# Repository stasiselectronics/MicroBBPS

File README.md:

# MicroBBPS
<h3> Integrated Micro Breadboard Power Supply</h3>
  
Here is the repository for the integrated version of the MicroBBPS. This design shares the same schematic and the same component placement as the solderless version. 

What makes this design special is that it has 26 rows of breadboard spaced plated through holes. This means you can take your breadboard experiments and directly transfer them to the integrated MicroBBPS to build a robust prototype that has easy power entry.

If you want to learn more about this particular version, be sure to check out the documentation webiste.

<h3><a href="https://stasiselectronics.github.io/MicroBBPS/">Read the Docs</a></h3>

<h4><a href="https://github.com/stasiselectronics/MicroBBPS/tree/main">Back to the solderless version repository</a></h4>

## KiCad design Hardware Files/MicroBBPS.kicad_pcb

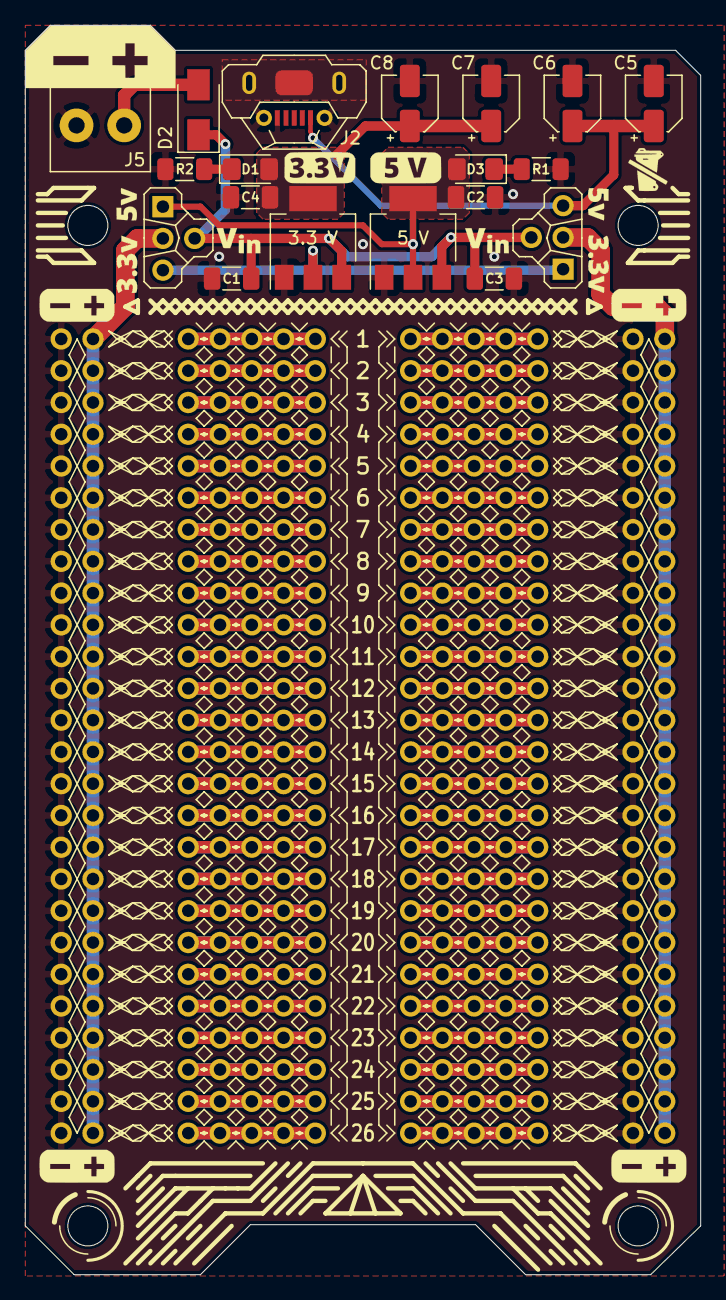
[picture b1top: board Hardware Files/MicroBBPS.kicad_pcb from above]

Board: 2 copper layers, 54.0 x 99.9 mm, 20 parts (0 on the bottom side), 9 nets.

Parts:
C1, C2, C3, C4: 220nF 50V; C_1206_3216Metric_Pad1.33x1.80mm_HandSolder
C5, C7: 10µF 16V; CP_Elec_4x5.4
C6, C8: 47µF 10V; CP_Elec_4x5.4
D1, D3: LED; D_1206_3216Metric_Pad1.42x1.75mm_HandSolder
D2: D; D_SMA
J1: Conn_01x06; Breadboard_Row_25
J2: USB_B_Micro; U-F-M5DD-Y-L
J5: Conn_01x02; WJ124-3.81-2P
J8, J9: 3PoleHeaderSwitch
R1: 56R 0.25W; R_1206_3216Metric_Pad1.30x1.75mm_HandSolder
R2: 0R; R_1206_3216Metric_Pad1.30x1.75mm_HandSolder
U1: NCP1117ST50T3G; SOT-223-3_TabPin2
U3: NCP1117ST33T3G; SOT-223-3_TabPin2

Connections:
+3V3: C4.1, C7.1, C8.1, D1.2, J8.1, J9.3, U3.2
+5V: C2.1, C5.1, C6.1, D3.2, J2.1, J8.3, J9.1, U1.2
/VoutLeft: J1.2, J9.2
/VoutRight: J1.6, J8.2
GND: C1.2, C2.2, C3.2, C4.2, C5.2, C6.2, C7.2, C8.2, J1.1, J1.5, J2.5, J2.6, J5.2, R1.2, R2.2, U1.1, U3.1
unnamed: D1.1, R2.1
unnamed: D2.2, J5.1
unnamed: D3.1, R1.1
VS: C1.1, C3.1, D2.1, J8.4, J9.4, U1.3, U3.3

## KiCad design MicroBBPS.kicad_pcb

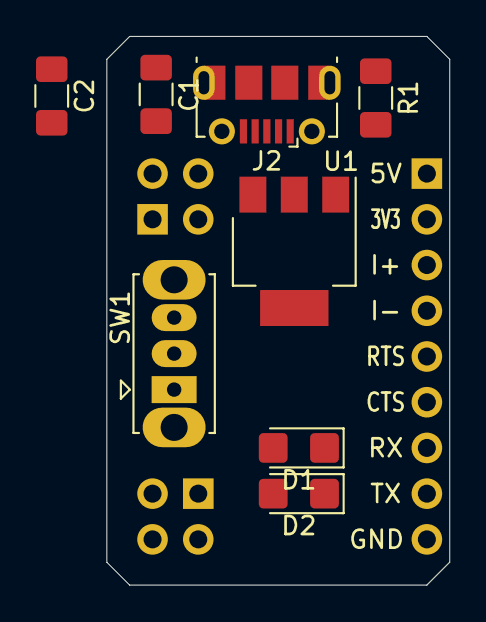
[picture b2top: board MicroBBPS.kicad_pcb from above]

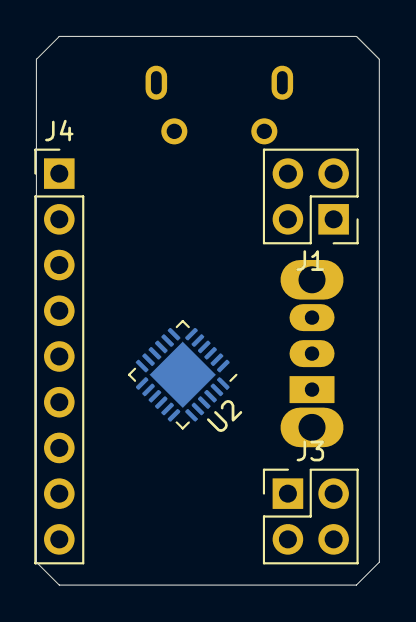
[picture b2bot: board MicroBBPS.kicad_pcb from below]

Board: 2 copper layers, 19.1 x 30.5 mm, 12 parts (4 on the bottom side), 4 nets, no tracks yet.

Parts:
C1, C2: C; C_1206_3216Metric_Pad1.42x1.75mm_HandSolder
D1, D2: LED; D_1206_3216Metric_Castellated
J1, J3: Conn_02x02_Odd_Even; PinHeader_2x02_P2.54mm_Vertical
J2: USB_B_Micro; USB_Micro-B_Molex-105017-0001
J4: Conn_01x09; PinHeader_1x09_P2.54mm_Vertical
R1: R; R_1206_3216Metric_Pad1.42x1.75mm_HandSolder
SW1: SW_SPDT; SW_Slide_1P2T_CK_OS102011MS2Q
U1: AZ1117-3.3; SOT-223-3_TabPin2
U2: CP2102N-A01-GQFN24; QFN-24-1EP_4x4mm_P0.5mm_EP2.6x2.6mm

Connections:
+3V3: C2.1, U1.2
+5V: C1.1, J4.1, R1.1, U1.3
GND: C1.2, C2.2, J2.5, J2.6, J4.9, U1.1
unnamed: J2.1, R1.2

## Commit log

2020-11-11 Moved files into Hardware Files folder
2020-11-11 Add new page layout
2020-11-11 update page layout
2021-01-07 Change board size to full breadboard length Move around components add 5v regulator add input terminal
2021-01-07 update layout add artwork update footprints
2021-01-07 Add footprint library add logos modify board shape add pours route some traces
2021-01-08 Add new parts
2021-01-08 Add new symbols
2021-01-08 add 3D model
2021-01-08 Change board shape Add more art finalize components finalize placement finalize routing
2021-01-09 Add part details
2021-01-09 Finalize components Finalize placement Finalize art Finalize BoM
2021-01-09 Add Gerbers & NC Drill Files
2021-01-09 change layer views
2021-01-13 Finalize A01 Design
2021-01-28 Add schematic PDF
2021-01-30 Update MPN and ordering code for Screw Terminal
2021-02-16 Add breadboard sections
2021-03-13 Clear Board Layout to redo it
2021-03-13 Place and route most components
2021-03-13 Finalize component placement and routing Board outline set to desired shape Breadboard rows in the right place Ready for artrwork
2021-03-15 Add power rail routes to both top and bottom layers
2021-03-15 Clean up drawing layers and dimensions
2021-03-20 Update board shape and add missing power rail routing
2021-03-20 Update Board shape and fix some routing
2021-03-20 Update routing to match main
2021-03-20 Fix board version mismatch
2021-03-20 Finalize routing and board shape
2021-03-20 Begin artwork
2021-03-20 Finalize artwork
2021-03-20 Finalize artwork, add missing files
2021-03-20 Match main version
2021-03-20 Bring in artwork from main version
2021-03-20 update D2 Position
2021-03-20 refill zones
2021-03-20 add details to Breadboard_Row_25.kicad_mod details
2021-03-20 Generate new gerbers
2021-03-20 fab file plotting
2021-03-20 add numbering to underside
2021-03-20 create gerbers
2021-03-20 update drill files
2021-03-20 update board size to fit in 100mm JLCPCB tolerance
2021-03-20 update gerbers and artwork
2021-03-20 update archive zip
2021-03-21 Finalize component part info and update bom
2021-03-21 Update part info for R2
2021-03-21 fix board shape
2021-03-21 Add missing fab files
2021-03-22 add images and update readme
2021-03-22 reduce image size and crop
2021-04-13 add new BOM
2021-04-13 add row spacing
2021-04-17 remove files
2021-04-17 Add pages template files
2021-04-18 update URL
2021-04-18 update config
2021-04-23 update splash image
2021-04-23 rename file
2021-04-23 update image
2021-04-23 update splash page content
2021-04-23 update splash page
2021-04-24 update schematic
2021-04-24 update BOM
2021-04-24 update documentation
2021-04-24 update content
2021-04-24 add assets
2021-04-24 add layout info
2021-04-25 add step file
2021-04-25 update gallery content
2021-04-25 add missing gallery page
2021-05-02 add assembly photos
2021-05-02 copy assembly content from 8 bit wifi vis
2021-05-08 add images
2021-05-08 add content to assembly instructions
2021-05-08 add voltage regulator image
2021-05-09 add header and footer
2021-05-14 Add BOM to cover both integrated and solderless versions
2021-05-17 update assembly instructions
2021-05-17 update site content
2021-08-15 add custom title to hero page
2021-08-19 fix typo
2021-08-29 add new bom for integrated version
